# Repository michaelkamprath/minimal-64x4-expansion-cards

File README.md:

# Expansion Cards for Minimal 64x4 Computer
This repository contains various expansion cards for the [Minimal 64x4 Home Computer](https://github.com/slu4coder/Minimal-64x4-Home-Computer/) design by Carsten Herting, known as [slu4 on YouTube](https://www.youtube.com/channel/UCXYQcMpUBT3aaQKfmAVJNow).

## Back Plane
The [back plane provided in this repository](./expansion-backplane/) allows for more than one expansion card to be connected to the Minimal 64x4. It also provides a more convenient barrel jack power connector with a on/off switch to power the Minimal 64x4.

## Cards

* [**Speech Synthesizer**](./speech-synthesizer/) - This board provides support for interfacing with a TMS5220C speech synthesizer. 
* [**Multiplier Card**](./multiplier/) - This board provides a hardware implimentation of 8-bit integer multiplications, significantly improving the speed of multiplications over software-implementations.
* [**Timer**](./timer/) - Counts the cycles of the Minimal 64x4's system clock to enable precision timing of events.
* [**Joystick Adapter**](./joystick-adapter/) - Reads an Atari 2600 style joystick. Currently a breadboard prototype built behind the [breadboard adapter](./expansion-backplane/hardware/breadboard-connector/).

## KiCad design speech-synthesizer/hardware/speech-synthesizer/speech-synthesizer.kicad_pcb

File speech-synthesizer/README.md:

# TMS5220 Speech Synthesizer for Minimal 64x4 Computer
This project creates a TMS5220-based speech synthesizer board for the [Minimal 64x4](https://github.com/slu4coder/Minimal-64x4-Home-Computer) expansion port. The high-level design criteria are:

1. **Accommodate the “slow memory” nature of the TMS5220** by using hardware to buffer the interactions between the CPU and the TMS5220 such that the CPU is free to do other tasks while the TMS5220 processes data. This contrasts with typical 1980s computer hardware designs, which would halt the CPU while the TMS5220 processed data.
2. **Only support “external” speech data; PHROMs are not supported.** Not supporting PHROMs greatly simplifies the board and saves money, as original PHROMs are hard to come by in the modern age. Most games of the 1980s did not use PHROM data, instead providing their own LPC-encoded speech data.

This board supports both the TMS5220 and TMS5220C variants of the speech synthesizer chip.

## Hardware Design
The board responds to three memory-mapped addresses (the board is adjustable to set the `_` value below, but it defaults to `0xC`):

* `0xFE_0` – **TMS5220 Command Register**
  This address allows the host computer to write data to the TMS5220’s command register, which is used for sending “external speech” data to the TMS5220. In general, the host computer will write certain TMS5220 commands and speech data to this address.

* `0xFE_1` – **TMS5220 Status Register**
  This address allows the host computer to fetch the internal TMS5220 status register. To do that, the host computer writes some data to this address (any value, as the value is not actually used) to start the sequence of events to get the internal status from the TMS5220. When this is done, the status value will be readable by the host computer at this address. The status data being ready is indicated by the board’s `BUSY` line, which is readable at the **Board Status Register**. The `BUSY` line will be asserted high from the moment this address is written to until the status value is ready to be read.

* `0xFE_2` – **Board Status Register**
  This address exposes several internal states of this board, independent of the TMS5220, and can be read by the host computer at any time. The individual bits within the byte value read are below. Of these lines, the host computer generally only interacts with the `/INT` and `BUSY` bits.

  * **bit 0 – `BUSY`**
    Indicates whether the TMS5220 or the board, in general, is working on something. The host computer should not interact with the TMS5220 Command or Status registers while this bit is high. A write to the Command or Status register while `BUSY` is high is silently dropped: the board does not queue it and gives no error, so always poll `BUSY` low before each write.
  * **bit 1 – `/INT`**
    The current value of the active-low interrupt line coming out of the TMS5220. When this bit is low, it indicates that the TMS5220 requires attention. The specific issue can be determined by reading the TMS5220 Status Register.
  * **bit 2 – `/READY`**
    The current value of the active-low `READY` line out of the TMS5220. Host computer software should use the `BUSY` line to arbitrate interaction with the board, but the `READY` line is exposed here for diagnostic purposes.
  * **bit 3 – `WS`**
    The current status of the `WS` flip flop (active high). Exposed for diagnostic purposes.
  * **bit 4 – `RS`**
    The current status of the `RS` flip flop (active high). Exposed for diagnostic purposes.

* `0xFE_3` – **TMS5220C Reset** – *TMS5220C PLD variant only*
  The TMS5220C variant can be reset by holding both the `/RS` and `/WS` lines low at the same time. This action has undefined results for the non-C TMS5220 variant, so there are two versions of the ATF22V10C configuration in [pld-files](./pld-files/), and the one programmed must match the chip that is fitted:

  * `minimal-64x4-speech-controller-tms5220.pld` – for the original TMS5220. Writes to `0xFE_3` are ignored, so `/RS` and `/WS` can never be asserted together.
  * `minimal-64x4-speech-controller-tms5220c.pld` – for the TMS5220C. Adds the reset described here. Do not use it with an original TMS5220.

  With the TMS5220C variant, the host computer times the reset:

  1. Poll `BUSY` low, then write to `0xFE_3`. The board asserts `/RS` and `/WS` together. Write `0xFF`: the value is driven onto the TMS5220C data lines for the duration of the reset, and `0xFF` is also the TMS5220 reset command.
  2. Wait for the reset hold time. `BUSY` reads high for the whole reset.
  3. Write to `0xFE_3` again (this write is accepted even though `BUSY` is high). The board releases `/WS`, then `/RS` one clock later.
  4. Poll `BUSY` low before using the board again.

  The reset logic has been compiled and simulated but not yet tested on hardware, and the hold time the TMS5220C needs has not been measured.

### Supporting Circuitry
Besides the bus interface described below, the board has a few parts that keep the TMS5220 and its audio output well behaved:

* **Data line pull-downs.** The eight data lines between the TMS5220 and the two 74HCT374 latches are only driven during a read or a write. The rest of the time neither the TMS5220 nor the write latch `U5` drives them, so `RN2` (47K, 9-pin bussed SIP) pulls them to ground to keep the inputs of the read latch `U4` from floating. `RN2` sits between the `U5` and `U4` sockets, where each of its pins is next to a data pin of one of the two latches. It is a close fit: the footprints leave about 3.2 mm between the two socket bodies, so use a network with a body no thicker than 2.5 mm.
* **Local decoupling for the TMS5220.** `C11` and `C12` (100 nF) decouple the TMS5220's `+5V` and `-5V` supply pins to ground right at pins 5 and 4, and `C13` (10 µF) adds bulk capacitance to the `-5V` rail from the converter module. `C13` is polarized: because it sits on a negative rail, its positive lead goes to ground.
* **Audio output.** The TMS5220's speaker pin is a current output. `R1` (1K8) converts it to a voltage and `C2` filters it, `C1` AC-couples the result to the 3.5 mm jack, and `R2` (100K) bleeds the jack side of `C1` to ground so that plugging in a cable does not pop.

### TMS5220 “Slow Memory” Issue
A key pin to understand on the TMS5220 is the `READY` signal at pin 18. The TMS5220 drives the `READY` pin low when it is ready to accept input or provide output to the host computer. When the `READY` pin is high, the TMS5220 is busy processing data and does not immediately act on—if not outright ignore—any interactions the CPU initiates. In many 1980s-era computers, the `READY` pin was connected to the CPU’s halt or wait-state pin, causing the CPU to stop while the TMS5220 processed data. This board takes a different approach. In some ways, this is necessary because the Minimal 64x4 has no line that would allow an accessory to pause or halt the CPU. However, this design choice is otherwise agnostic of that limitation.

As a result, data interactions between the host computer and the TMS5220 must be cached to handle the timing differences. The key to caching these CPU interactions is the ATF22V10C programmable logic chip and the 74HCT74 flip flops. The flip flops hold the `/WS` and `/RS` signals on the TMS5220, and the ATF22V10C is programmed to create a state machine that manages these flip flops. For example, here is the sequence of events for writing a byte of data to the TMS5220:

1. When the address bus is set to the memory-mapped address of `0xFEC0`, the 74HCT688s will assert this `MMAP` line, and the `M0` and `M1` address lines will be 0. To write to the TMS5220, the host computer `/RI` line will be asserted. The ATF22V10C’s programmable logic then asserts `WS_CLK`, which is the clock line that drives the `WS` flip flop, in turn asserting the active-low `/WS` line to the TMS5220. This tells the TMS5220 that we want to write data to its data lines.
2. At the same time `WS_CLK` causes the `WS` flip flop to set its state, `WS_CLK` also causes the data bus input 74HCT374 flip flop to load the contents of the host computer’s data bus. Because of this, the expansion board can capture and hold the data bus value the host computer is writing to the TMS5220, allowing the host computer to move on to other tasks while this flip flop holds the data bus value. Furthermore, the `/WS` line to the TMS5220 also drives the output enable on the 74HCT374 octal flip flop, so the buffered data will be held and driven onto the board’s internal data bus for the entire time `/WS` is low—even as the host computer does other work. This is the essence of the “slow memory” issue: the TMS5220 requires several host-computer clock cycles to read in the data, and its data lines must be held for the entire duration. The 74HCT374 flip flop buffers the data and holds the lines active as long as needed.
3. In response to the `/WS` line being asserted, the TMS5220 drives the `READY` line high. When this occurs, the ATF22V10C waits until the `READY` line transitions from high to low, which indicates that the TMS5220 has finished processing the input data. When the `READY` line goes low, the ATF22V10C then asserts `WS_RST`, the reset line for the `WS` flip flop. This brings `/WS` high, which tells the TMS5220 that the write operation is complete. It also disables the output enable on the 74HCT374 that was buffering the data. In this way, `/WS` remains asserted until the TMS5220 indicates it is done reading the data from the buffers, as indicated by the `READY` line.
4. During this entire sequence, the ATF22V10C asserts the `BUSY` line for the board, which can be read by the host computer at address `0xFE_2` via the 74HCT245. This allows the host computer to query the board to see if the TMS5220 is done processing data.

A similar sequence is used when reading data from the TMS5220, centered around the `/RS` line.

### Undocumented Timing Issues
The TMS5220 appears to have some timing requirements that are not documented in its datasheet. These requirements were exposed by the Minimal 64x4, which runs at a clock speed faster than the typical host computers for which the TMS5220 was designed. These undocumented timing requirements were determined empirically and could likely be tweaked further:

* **Read Cycle for Status Transfers to External Speech Data Write**
  The datasheet indicates that the `t_wait` after `/RS` goes high is 12 µs. However, I found that something closer to 175 µs was needed between a status read and a subsequent external speech data write.

* **External Speech Data Write to Read Cycle for Status Transfers**
  Similarly, extra time is needed between writing external speech data and then reading the TMS5220 status. Again, I found that about 175 µs was needed.

These values were “tweaked until it worked.” The issues seem related to switching modes of interaction with the TMS5220. By contrast, writing an external speech data byte after a prior external speech data byte does adhere to the timing diagrams in the TMS5220 datasheet. Further experimentation might uncover better or smaller delays for these undocumented requirements.

## Software Design
The provided `speechlib.min64x4` file contains all the subroutines needed to use this board on the Minimal 64x4 home computer:

* `speech_init`
  Call this to initialize the board.

* `speak_synchronous`
  Speaks the LPC data in a passed buffer synchronously. Push the following arguments on the stack (in push order):
  1. **Buffer End Address** – 2-byte end address of the data buffer
  2. **Buffer Start Address** – 2-byte start address of the data buffer

* `speech_start`
  Speaks the LPC data in a passed buffer asynchronously, after synchronously waiting for any currently active talking to finish. Push the following arguments on the stack (in push order):
  1. **Buffer End Address** – 2-byte end address of the data buffer
  2. **Buffer Start Address** – 2-byte start address of the data buffer

* `speech_start_if_not_talking`
  Speaks the LPC data in a passed buffer asynchronously if there is no currently active speech. Push the following arguments on the stack (in push order):
  1. **Buffer End Address** – 2-byte end address of the data buffer
  2. **Buffer Start Address** – 2-byte start address of the data buffer

* `speech_update_buffer`
  Call this periodically (about every 1 ms) to enable asynchronous speech. No arguments.

* `speech_get_status`
  Gets the contents of the TMS5220 status register, which is returned in the `A` register. The following bit masks are defined to help interpret the results:
  * `SPEECH_STATUS_TALK` – The TMS5220 is currently talking.
  * `SPEECH_STATUS_BUFFER_LOW` – The TMS5220 FIFO buffer is half-empty. More LPC data needs to be sent.
    *_Note_*: The `speech_update_buffer` function automatically updates the FIFO if needed.
  * `SPEECH_STATUS_BUFFER_EMPTY` – The TMS5220 FIFO buffer is empty.

# Compiling the Software
All software found in the [software](./software/) directory is compiled with [BespokeASM](https://github.com/michaelkamprath/bespokeasm), which supports the Minimal 64x4. [Carsten Herting](https://github.com/slu4coder), the creator of the Minimal 64x4, also provides an assembler for it, but that assembler is quite minimal. One key shortcoming is the inability to import library code into the current compilation. BespokeASM enables importing libraries and includes several other features that this project’s software depends on.

To compile the speech code in this repository, use the following command:

```sh
bespokeasm compile -c /path/to/bespokeasm/examples/slu4-minimal-64x4/slu4-minimal-64x4.yaml -n -p -t intel_hex lpc_player.min64x4
```
Where `/path/to/bespokeasm` is the path to the BespokeASM repository on your computer. This will produce an Intel HEX representation of the compiled program, which can then be sent to the Minimal 64x4 using its `receive` command.

# Resources
The following resources I found useful when putting together this project

* [TMS5220 Datasheet](./datasheets/tms5220.pdf) - Always consult the datasheet first.
* [Thierry Nouspikel's "The Speech Synthesizer module"](https://www.unige.ch/medecine/nouspikel/ti99/speech.htm) - A detailed overview of how the TMS5220 is used in the TI 99/4a.
* [TI 99/4a Development forum on AtariAge](https://forums.atariage.com/topic/352156-looking-for-help-on-tms5220-circuit-software-design-and-usage/) - These folks are legends, helpful and knowledgable about anything related to Texas Instruments.

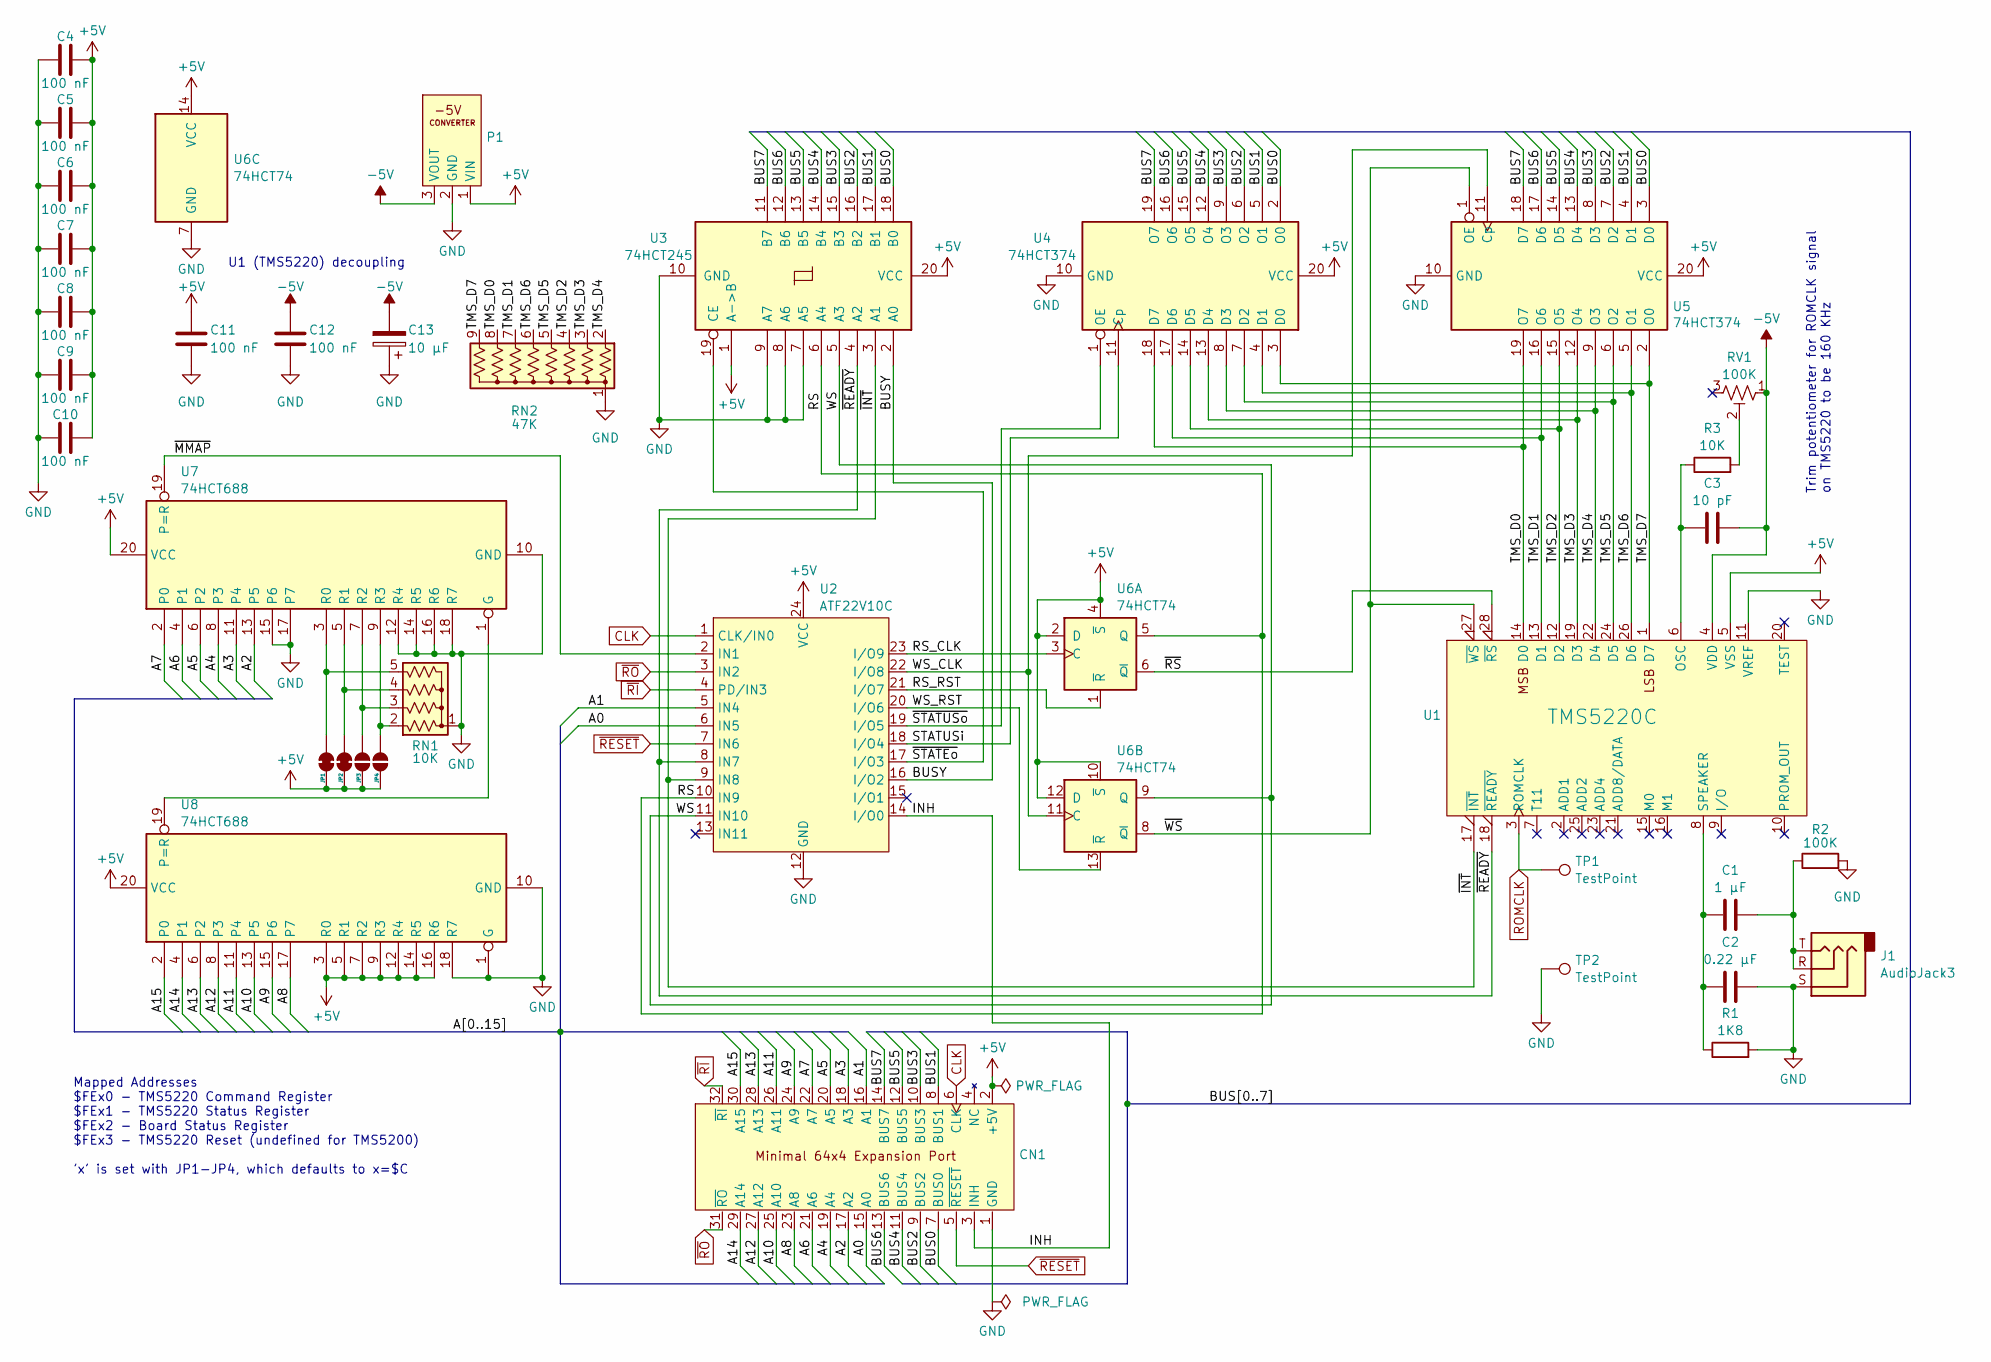
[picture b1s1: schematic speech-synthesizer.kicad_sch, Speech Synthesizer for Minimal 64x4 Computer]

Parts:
C1: 1 µF; C_Disc_D4.7mm_W2.5mm_P5.00mm
C2: 0.22 µF; C_Disc_D4.7mm_W2.5mm_P5.00mm
C3: 10 pF; C_Disc_D5.0mm_W2.5mm_P2.50mm
C4, C5, C6, C7, C8, C9, C10, C11, C12: 100 nF; C_Disc_D3.4mm_W2.1mm_P2.50mm
C13: 10 µF; CP_Radial_D5.0mm_P2.00mm
CN1: PinHeader_2x16_P2.54mm_Horizontal
J1: AudioJack3; Jack_3.5mm_CUI_SJ1-3523N_Horizontal
JP1, JP2: SolderJumper_2_Bridged; SolderJumper-2_P1.3mm_Bridged_RoundedPad1.0x1.5mm
JP3, JP4: SolderJumper_2_Open; SolderJumper-2_P1.3mm_Open_RoundedPad1.0x1.5mm
P1: -5V_Converter
R1: 1K8; R_Axial_DIN0207_L6.3mm_D2.5mm_P10.16mm_Horizontal
R2: 100K; R_Axial_DIN0207_L6.3mm_D2.5mm_P10.16mm_Horizontal
R3: 10K; R_Axial_DIN0207_L6.3mm_D2.5mm_P10.16mm_Horizontal
RN1: 10K; R_Array_SIP5
RN2: 47K; R_Array_SIP9
RV1: 100K; Potentiometer_Vishay_T73YP_Vertical
TP1, TP2: TestPoint; TestPoint_Pad_D2.0mm
U1: TMS5220C; DIP-28_W15.24mm_Socket
U2: ATF22V10C; DIP-24_W7.62mm_Socket
U3: 74HCT245; DIP-20_W7.62mm_Socket
U4, U5: 74HCT374; DIP-20_W7.62mm_Socket
U6: 74HCT74; DIP-14_W7.62mm_Socket
U7, U8: 74HCT688; DIP-20_W7.62mm_Socket

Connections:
+5V: C4.2, C5.2, C6.2, C7.2, C8.2, C9.2, C10.2, C11.1, CN1.2 (+5V), JP1.1 (A), JP2.1 (A), JP3.1 (A), JP4.1 (A), P1.1 (VIN), U1.5 (VSS), U2.24 (VCC), U3.1 (A->B), U3.20 (VCC), U4.20 (VCC), U5.20 (VCC), U6.2 (D), U6.4 (~S), U6.10 (~S), U6.12 (D), U6.14 (VCC), U7.20 (VCC), U8.3 (R0), U8.5 (R1), U8.7 (R2), U8.9 (R3), U8.12 (R4), U8.14 (R5), U8.16 (R6), U8.20 (VCC)
-5V: C3.1, C12.1, C13.2, P1.3 (VOUT), RV1.1, U1.4 (VDD)
/A0: CN1.15 (A0), U2.6 (IN5)
/A1: CN1.16 (A1), U2.5 (IN4)
/A2: CN1.17 (A2), U7.13 (P5)
/A3: CN1.18 (A3), U7.11 (P4)
/A4: CN1.19 (A4), U7.8 (P3)
/A5: CN1.20 (A5), U7.6 (P2)
/A6: CN1.21 (A6), U7.4 (P1)
/A7: CN1.22 (A7), U7.2 (P0)
/A8: CN1.23 (A8), U8.17 (P7)
/A9: CN1.24 (A9), U8.15 (P6)
/A10: CN1.25 (A10), U8.13 (P5)
/A11: CN1.26 (A11), U8.11 (P4)
/A12: CN1.27 (A12), U8.8 (P3)
/A13: CN1.28 (A13), U8.6 (P2)
/A14: CN1.29 (A14), U8.4 (P1)
/A15: CN1.30 (A15), U8.2 (P0)
/BUS0: CN1.7 (BUS0), U3.18 (B0), U4.2 (O0), U5.3 (D0)
/BUS1: CN1.8 (BUS1), U3.17 (B1), U4.5 (O1), U5.4 (D1)
/BUS2: CN1.9 (BUS2), U3.16 (B2), U4.6 (O2), U5.7 (D2)
/BUS3: CN1.10 (BUS3), U3.15 (B3), U4.9 (O3), U5.8 (D3)
/BUS4: CN1.11 (BUS4), U3.14 (B4), U4.12 (O4), U5.13 (D4)
/BUS5: CN1.12 (BUS5), U3.13 (B5), U4.15 (O5), U5.14 (D5)
/BUS6: CN1.13 (BUS6), U3.12 (B6), U4.16 (O6), U5.17 (D6)
/BUS7: CN1.14 (BUS7), U3.11 (B7), U4.19 (O7), U5.18 (D7)
/BUSY: U2.16 (I/O2), U3.2 (A0)
/INH: CN1.3 (INH), U2.14 (I/O0)
/RS: U2.10 (IN9), U3.6 (A4), U6.5 (Q)
/RS_CLK: U2.23 (I/O9), U6.3 (C)
/RS_RST: U2.21 (I/O7), U6.1 (~R)
/STATUSi: U2.18 (I/O4), U4.11 (Cp)
/TMS_D0: RN2.8 (R7), U1.14 (D0), U4.18 (D7), U5.19 (O7)
/TMS_D1: RN2.7 (R6), U1.13 (D1), U4.17 (D6), U5.16 (O6)
/TMS_D2: RN2.4 (R3), U1.12 (D2), U4.14 (D5), U5.15 (O5)
/TMS_D3: RN2.3 (R2), U1.19 (D3), U4.13 (D4), U5.12 (O4)
/TMS_D4: RN2.2 (R1), U1.22 (D4), U4.8 (D3), U5.9 (O3)
/TMS_D5: RN2.5 (R4), U1.24 (D5), U4.7 (D2), U5.6 (O2)
/TMS_D6: RN2.6 (R5), U1.26 (D6), U4.4 (D1), U5.5 (O1)
/TMS_D7: RN2.9 (R8), U1.1 (D7), U4.3 (D0), U5.2 (O0)
/WS: U2.11 (IN10), U3.5 (A3), U6.9 (Q)
/WS_CLK: U2.22 (I/O8), U5.11 (Cp), U6.11 (C)
/WS_RST: U2.20 (I/O6), U6.13 (~R)
/~INT: U1.17 (~INT), U2.9 (IN8), U3.3 (A1)
/~MMAP: U2.2 (IN1), U7.19 (P=R)
/~READY: U1.18 (~READY), U2.8 (IN7), U3.4 (A2)
/~RS: U1.28 (~RS), U6.6 (~Q)
/~STATEo: U2.17 (I/O3), U3.19 (CE)
/~STATUSo: U2.19 (I/O5), U4.1 (OE)
/~WS: U1.27 (~WS), U5.1 (OE), U6.8 (~Q)
CLK: CN1.6 (CLK), U2.1 (CLK/IN0)
GND: C2.2, C4.1, C5.1, C6.1, C7.1, C8.1, C9.1, C10.1, C11.2, C12.2, C13.1, CN1.1 (GND), J1.S, P1.2 (GND), R1.2, R2.2, RN1.1 (common), RN2.1 (common), TP2.1, U1.11 (VREF), U2.12 (GND), U3.7 (A5), U3.8 (A6), U3.9 (A7), U3.10 (GND), U4.10 (GND), U5.10 (GND), U6.7 (GND), U7.10 (GND), U7.12 (R4), U7.14 (R5), U7.15 (P6), U7.16 (R6), U7.17 (P7), U7.18 (R7), U8.1 (G), U8.10 (GND), U8.18 (R7)
unnamed: C1.2, J1.R, J1.T, R2.1
unnamed: JP1.2 (B), RN1.5 (R4), U7.3 (R0)
unnamed: JP2.2 (B), RN1.4 (R3), U7.5 (R1)
unnamed: JP3.2 (B), RN1.3 (R2), U7.7 (R2)
unnamed: JP4.2 (B), RN1.2 (R1), U7.9 (R3)
unnamed: R3.2, RV1.2
unnamed: C3.2, R3.1, U1.6 (OSC)
unnamed: C1.1, C2.1, R1.1, U1.8 (SPEAKER)
unnamed: U7.1 (G), U8.19 (P=R)
ROMCLK: TP1.1, U1.3 (ROMCLK)
~RESET: CN1.5 (~RESET), U2.7 (IN6)
~RI: CN1.32 (~RI), U2.4 (PD/IN3)
~RO: CN1.31 (~RO), U2.3 (IN2)

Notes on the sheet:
Trim potentiometer for ROMCLK signal on TMS5220 to be 160 KHz
Mapped Addresses $FEx0 - TMS5220 Command Register $FEx1 - TMS5220 Status Register $FEx2 - Board Status Register $FEx3 - TMS5220 Reset (undefined for TMS5200) 'x' is set with JP1-JP4, which defaults to x=$C
U1 (TMS5220) decoupling

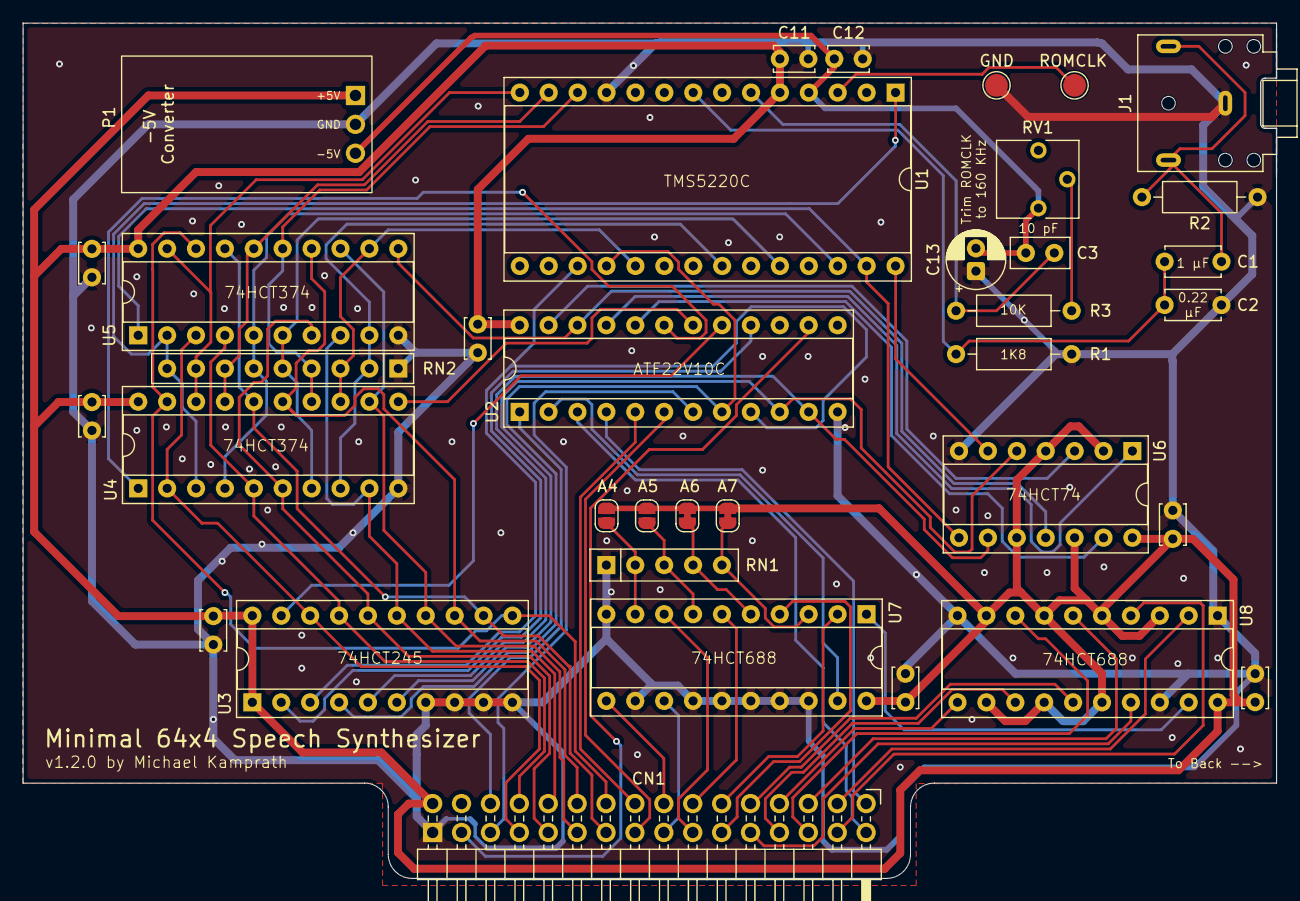
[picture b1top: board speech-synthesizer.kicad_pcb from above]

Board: 2 copper layers, 110.2 x 75.2 mm, 36 parts (0 on the bottom side), 65 nets.

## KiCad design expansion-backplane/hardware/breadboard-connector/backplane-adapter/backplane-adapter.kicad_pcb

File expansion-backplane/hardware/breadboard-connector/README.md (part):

# Minimal 64x4 Breadboard Prototyping Adapter

Bench tooling for prototyping Minimal 64x4 expansion cards on a solderless breadboard before designing their PCBs. The adapter plugs into a slot of the [expansion backplane](../expansion-backplane/), or directly into the Minimal's expansion port, and brings a buffered, address-decoded view of the expansion bus to a breadboard over a ribbon cable.

The design requirements are in [`breadboard-adapter-design-prompt.md`](breadboard-adapter-design-prompt.md).

## Boards

| Directory | Board | Role |
|---|---|---|
| [`backplane-adapter/`](backplane-adapter/) | Board A | Plugs into a backplane slot. Buffers all signals, decodes the `$FE` page plus a switch-selected 16-byte base window, drives INH, and protects the Minimal from the breadboard. |
| [`breadboard-breakout/`](breadboard-breakout/) | Board B | Receives the cable and the twisted power pair from Board A's J2, and brings every signal to labeled 0.1 inch headers that plug into a breadboard. |

The two boards are separate KiCad projects. Both use the shared symbol and footprint libraries in [`kicad-libraries/`](../../../kicad-libraries/).

## Cable pinout

**This table is the single source of truth for the ribbon cable.** The two boards are in separate KiCad projects, so nothing checks automatically that both ends agree. Any change to the cable connector on either schematic must be made here first, then applied to both boards.

Cable: 40-way, 0.05 inch pitch IDC ribbon, 30 to 45 cm (see [Cable length](#cable-length) for what the length costs). Every signal conductor has a ground conductor on each side. The clock and both strobes must sit between two grounds.

Status: **proposed**, as drawn on Board A J1. Every odd pin is ground, so along the ribbon every signal (even pin) sits between two grounds. Pin 40 is an extra ground. No logic power rides on the ribbon. `~MATCH` is active low; `INH_REQ` is active high.

| Pin | Signal | Pin | Signal |
|---|---|---|---|
| 1 | GND | 2 | A0 |
| 3 | GND | 4 | A1 |
| 5 | GND | 6 | A2 |
| 7 | GND | 8 | A3 |
| 9 | GND | 10 | ~MATCH (16-byte base window) |
| 11 | GND | 12 | ~RO |
| 13 | GND | 14 | ~RI |
| 15 | GND | 16 | CLK |
| 17 | GND | 18 | INH_REQ (breadboard to adapter) |
| 19 | GND | 20 | BUS0 |
| 21 | GND | 22 | BUS1 |
| 23 | GND | 24 | BUS2 |
| 25 | GND | 26 | BUS3 |
| 27 | GND | 28 | BUS4 |
| 29 | GND | 30 | BUS5 |
| 31 | GND | 32 | BUS6 |
| 33 | GND | 34 | BUS7 |
| 35 | GND | 36 | ~RESET (unbuffered pass-through) |
| 37 | GND | 38 | USER (unbuffered pass-through) |
| 39 | GND | 40 | GND |

Main +5 V and ground to the breadboard use a separate 20 or 22 AWG twisted pair from Board A's J2 to Board B, not the ribbon.

## Using the adapter

### Power

- **JP1 fitted (normal use):** the breadboard is powered from the backplane, or from the Minimal when Board A plugs directly into its expansion port, through F1 and J2. One supply powers both sides, so they always switch on and off together. F1, a 0.5 A resettable fuse, limits what a breadboard fault can draw through the Minimal's or the backplane's 5 V path; it trips at about 1 A and resets once the fault is removed and it cools. A prototype that needs more than a few hundred mA should use its own supply on Board B's J3, with JP1 removed. When Board A plugs directly into the Minimal, the computer may be running from its UART's USB power, which leaves only a few hundred mA for the breadboard.
- **JP1 removed:** J2's +5 V is disconnected and the breadboard needs its own supply. Ground stays common through J2 and the ribbon. **Switch both supplies on and off together.** If one side is powered and the other is not, the powered side's drivers push current through the 33 Ω termination into the unpowered chips' input protection diodes, on the order of 100 mA per line. That is an operating error, not a design fault, but it can damage parts on either side.

### Enable switch

SW2 is **closed for enabled**. With it open, the adapter is disconnected from the bus: the data transceiver (U4) is off and INH is held low. A freshly built adapter therefore does nothing until SW2 is switched on.

## Who drives the data bus

This document names bus operations from the CPU's side and always says "CPU read" or "CPU write". Seen from the prototype, each one is the opposite action on the data bus:

| Operation | Strobe | Who drives the data bus | What the prototype does | INH_REQ |
|---|---|---|---|---|
| **CPU read** | `~RO` low, `~RI` high | The prototype (through U4, toward the backplane) | Puts its data on the bus | The prototype must raise it |
| **CPU write** | `~RI` low | The CPU (through U4, toward the breadboard) | Takes the data from the bus on the rising edge of CLK | Not used |

The strobe names follow the Minimal's RAM: `~RO` is "RAM out" (the addressed device drives the bus) and `~RI` is "RAM in" (the addressed device takes data from the bus).

## Rules for a breadboard prototype

The adapter keeps a misbehaving breadboard from damaging the Minimal, but a prototype that follows these rules behaves like a real card and avoids fighting the adapter's own drivers:

1. **Decode from `~MATCH` and A0..A3.** `~MATCH` is low for every access to the 16-byte window set by SW1. A4..A15 are not on the cable.
2. **Raise INH_REQ only for a CPU read of one of your registers** (the prototype drives the data bus), qualified by `~RO` low and `~RI` high, the same way the [timer card's PLD](../../../timer/pld-files/timer.pld) qualifies its INH. The adapter ignores INH_REQ outside CPU reads anyway, but qualifying it keeps the prototype honest for its final PCB.
3. **Drive the breadboard's data bus only while `~RO` is low** (and you are raising INH_REQ). Outside those cycles the adapter's U4 drives the cable side of the data bus toward the breadboard, so a prototype that drives early fights U4 through the 33 Ω termination: current-limited, no damage, but messy waveforms.
4. **Keep the decode fast.** The prototype has about 14 ns, worst case, from its inputs to INH_REQ (see the timing estimate below). One pass through a -7 PLD (ATF16V8C or ATF22V10C) or two 74AHCT gates fits. A 74HC decode chain does not.
5. **Capture CPU writes (the CPU drives the data bus) on the rising edge of CLK while `~RI` is low**, not on `~RI`'s rising edge. See the CPU write timing below.
6. **Never drive `~RESET` high.** It is wired straight through to the Minimal's reset line. Only pull it low (Board B's button does this).

## Drawing a prototype's schematic

The shared symbol library (`kicad-libraries/minimal-64x4.kicad_sym`) has a symbol, `min-64x4-breadboard-adapter`, that stands for the whole adapter as the breadboard sees it. A prototype's schematic uses it in place of the expansion connector and does not need to show Board A or Board B.

- **Signals:** A0..A3, `~MATCH`, `~RO`, `~RI` and CLK are outputs of the adapter. BUS0..BUS7 are bidirectional. INH_REQ is an input to the adapter; Board A pulls it low, so a prototype that never drives the data bus (the CPU only writes to it) can leave it unconnected (mark it no-connect).
- **Power:** +5 V and GND are power inputs, as on the expansion-port symbol, so add `PWR_FLAG` symbols to those nets.
- **Pin numbers** are Board B's pin positions in DIP-24 order, looking at the top of the board with the cable connector away from you: 1 to 12 down the left row (+5 V, GND, USER, `~RESET`, BUS7..BUS0), 13 to 24 up the right row (GND, INH_REQ, CLK, `~RI`, `~RO`, `~MATCH`, A3..A0, GND, +5 V). The rows are 7.62 mm apart, so a DIP-24 socket footprint matches the pins if a later PCB should accept Board B directly.
- The symbol is excluded from the BOM and from the board by default.

## Building a prototype's logic

### Timing budget

A prototype's logic has two budgets, both counted from the moment its inputs arrive on the breadboard. The inputs that matter are the later of `~MATCH` and `~RO`, after U3 and the ribbon. They arrive about 57 ns after the CPU's clock edge typically, 67 ns at the 25 °C maximum, and 76 ns at the −40..85 °C maximum. On a CPU read, the prototype's data must be on the backplane by about 115 ns (see the timing estimate below).

| From inputs at the breadboard to... | Typ | Max 25 °C | Max −40..85 °C |
|---|---|---|---|
| **INH_REQ out** (X in the timing estimate) | 39 ns | 24 ns | **14 ns** |
| **Prototype's data driven onto the cable** (CPU read) | 50 ns | 37 ns | **27 ns** |

The second budget covers the ribbon and U4's A-to-B delay on the way back to the backplane.

- **ATF16V8C-7 (7.5 ns):** fits both budgets, with 7 ns to spare at the worst case. A -10 part also fits. A -15 part misses the worst case by about 1 ns but is fine at room temperature.
- **Data drivers:** after the PLD's 7.5 ns, about 20 ns remain for the output enable of whatever drives the data bus. A 74AHCT245 or 74AHCT541 (16 ns max) fits. For anything slower, such as a counter's own output enable, check its datasheet. If it is over about 20 ns, put a 74AHCT245 or 541 in front of it.
- **INH release** rarely depends on the prototype. Board A's PLD raises INH only while INH_REQ is high, `~RO` is low, `~RI` is high and its own decode matches the window, and drops it as soon as any one of those stops being true. Leaving the window and the end of the CPU read are both seen on Board A directly. The one case that waits for the prototype is described under [INH release](#inh-release-and-the-following-opcode-fetch).

### A nominal ATF16V8C

[`pld-files/breadboard-prototype-template.pld`](pld-files/breadboard-prototype-template.pld) is a starting point that compiles with galette. Its example register map uses the window `$FEx0..$FEx3`, where `x` is the base nibble set by SW1:

| Address | CPU write | CPU read |
|---|---|---|
| `$FEx0` | WR0 | RD0 (INH_REQ) |
| `$FEx1` | WR1 | RD1 (INH_REQ) |
| `$FEx2` | WR2 | RD2 (INH_REQ) |
| `$FEx3` | WR3 | nothing; the CPU reads RAM |
| `$FEx4..$FExF` | nothing | nothing |

How it is put together:

- **INH_REQ repeats the CPU-read decode instead of ORing the RD outputs.** The timer card's PLD does `INH = /OE0 + /OE1 + ...`, which feeds outputs back into the array: a second PLD pass. On the breadboard that would double X to 15 ns, over the 14 ns worst-case budget.
- **The CPU-write strobes (WR0..WR3) are registered on CLK with `~RI` low**, like `WS_CLK.R` on the speech card. Each strobe rises one clock-to-output delay after the cable's CLK edge and lasts exactly one cycle.
- **Clock each data latch (74AHCT374 or 574) on its strobe's rising edge.** The CPU's data stays on the bus for roughly 25 ns after that edge. The falling edge comes a cycle later, after the data is gone, which is why the strobes are active high.
- **Registered mode costs two pins.** Pin 1 becomes the register clock and pin 11 the registered outputs' `/OE`, which must be tied to GND. That leaves 8 outputs: in the template, INH_REQ, four CPU-write strobes and three CPU-read enables (RD0..RD2, which turn on the prototype's bus drivers). A prototype with no registers for the CPU to write gets pins 1 and 11 back as inputs.
- **`~RESET` is on pin 9** for clearing prototype state. No equation in the template uses it yet.
- **A0..A3 hold time at the CPU-write sample is tight**, by a few ns, on every card. The Minimal can change the address 10 to 15 ns after the clock edge, about when the port's CLK, one 74HC32 behind the CPU's clock, arrives. The adapter makes this no worse, because CLK and A0..A3 pass through U3 together.

## Timing estimate (CPU read through the adapter)

### The Minimal's CPU read cycle

From the "Timing Signals" section of the [Minimal 64x4 manual](https://docs.google.com/document/d/1-nDv_8WEG1FrlO3kEK0icoYo-Z-jlhpCMiCstxGOCjQ/edit?usp=sharing). Its diagram was measured on the author's board at 8.3 MHz and 5 V, with every time referenced to the CPU clock's rising edge at the start of the cycle. The [Revision 1.1 schematic](https://github.com/slu4coder/Minimal-64x4-Home-Computer/blob/main/Revision%201.1/Schematics.pdf) shows how the port's signals connect:

- **`~RO` and `~RI`** (port pins 31 and 32) come straight from the control-word FLASH (U21), with no gating. They are the same `~RO` that drives the RAM's and FLASH's output enables. Port `~RI` is the control-word level, not the RAM write pulse: the SRAM's `~WE` is `~RI_PLS`, which is `~RI` ORed with a short clock pulse (U7D) near the edge that ends the cycle.
- **CLK** (port pin 6) is `CLK_PC` through one 74HC32 gate (U33C), so it lags the CPU's clock edge by one gate delay.
- **INH** (port pin 3) has a 4.7 kΩ pulldown and drives the SRAM's `~CE` directly. In the `$FE` page the FLASH is already deselected by A15.

| Event | Time after the rising edge |
|---|---|
| Address lines (MAR outputs) change | 0 to 15 ns |
| Control word settles, including the port's `~RO` and `~RI` | 45 to 50 ns, and stays until 45 to 50 ns into the next cycle |
| The Minimal's own RAM drives its data onto the bus | about 80 ns |
| Bus sampled | at the next rising edge, with 10 ns setup required |

At 8 MHz (125 ns cycle), **on a CPU read, the addressed device's data must be on the backplane bus by about 115 ns.** The address can change in the same cycle as the CPU read: in `LDB` the MAR is loaded at the edge that starts the CPU read step, so the address path starts at 15 ns, not at 0. These are measured, typical values. The manual notes that 74HC switching slows by about 20 % at 4.5 V.

### The adapter's two paths

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
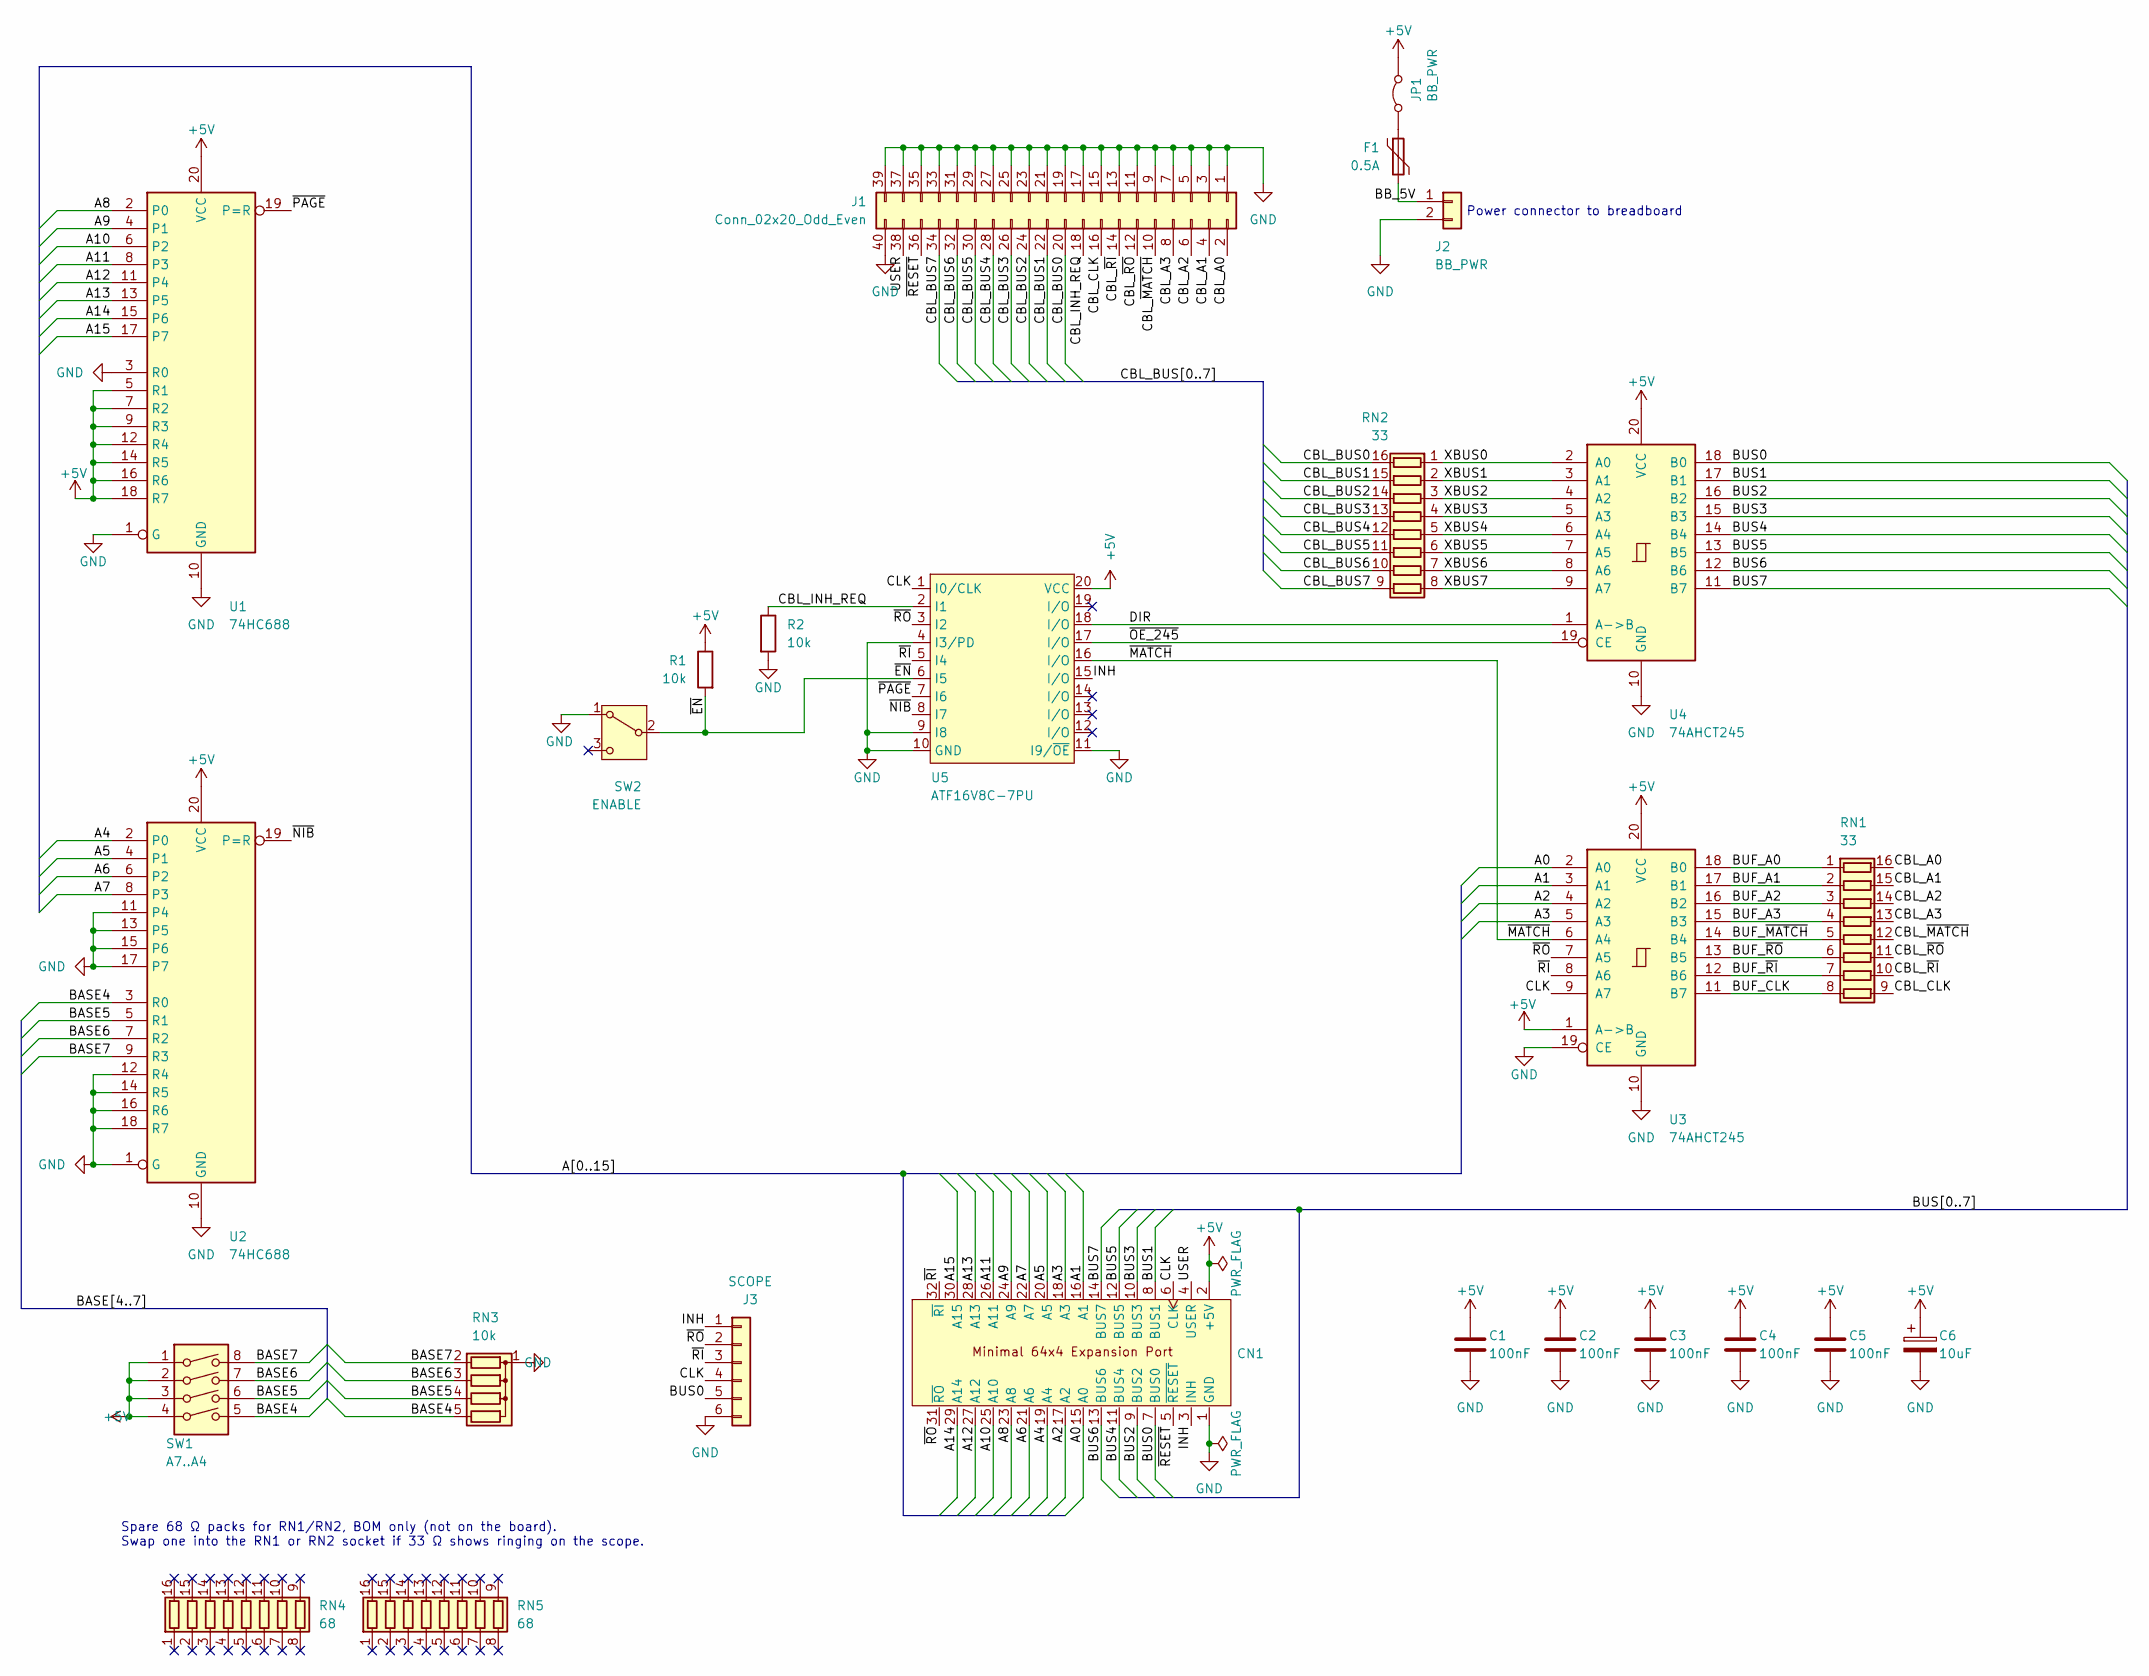
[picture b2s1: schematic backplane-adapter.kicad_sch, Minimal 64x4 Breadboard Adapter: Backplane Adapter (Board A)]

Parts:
C1, C2, C3, C4, C5: 100nF; C_Disc_D3.4mm_W2.1mm_P2.50mm
C6: 10uF; CP_Radial_D5.0mm_P2.00mm
CN1: Minimal64x4_Expansion_Card_Connector
F1: 0.5A; Fuse_Bourns_MF-RHT050; Manufacturer Part Number Bourns MF-RHT050
J1: Conn_02x20_Odd_Even; IDC-Header_2x20_P2.54mm_Horizontal; Manufacturer Part Number Sullins SBH11-PBPC-D20-RA-BK
J2: BB_PWR; TerminalBlock_Phoenix_MKDS-1,5-2-5.08_1x02_P5.08mm_Horizont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
J3: SCOPE; PinHeader_1x06_P2.54mm_Horizontal
JP1: BB_PWR; PinHeader_1x02_P2.54mm_Vertical
R1, R2: 10k; R_Axial_DIN0207_L6.3mm_D2.5mm_P7.62mm_Horizontal
RN1, RN2: 33; DIP-16_W7.62mm_Socket; Mouser Part Number 652-4116R-1-330LF
RN3: 10k; R_Array_SIP5
RN4, RN5: 68; DIP-16_W7.62mm_Socket; Mouser Part Number 652-4116R-1-680LF
SW1: A7..A4; SW_DIP_SPSTx04_Slide_9.78x12.34mm_W7.62mm_P2.54mm
SW2: ENABLE; SW_Slide_SPDT_Angled_CK_OS102011MA1Q
U1, U2: 74HC688; DIP-20_W7.62mm_Socket
U3, U4: 74AHCT245; DIP-20_W7.62mm_Socket
U5: ATF16V8C-7PU; DIP-20_W7.62mm_Socket

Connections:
+5V: C1.1, C2.1, C3.1, C4.1, C5.1, C6.1, CN1.2 (+5V), JP1.2 (B), R1.1, SW1.1, SW1.2, SW1.3, SW1.4, U1.5 (R1), U1.7 (R2), U1.9 (R3), U1.12 (R4), U1.14 (R5), U1.16 (R6), U1.18 (R7), U1.20 (VCC), U2.20 (VCC), U3.1 (A->B), U3.20 (VCC), U4.20 (VCC), U5.20 (VCC)
/A0: CN1.15 (A0), U3.2 (A0)
/A1: CN1.16 (A1), U3.3 (A1)
/A2: CN1.17 (A2), U3.4 (A2)
/A3: CN1.18 (A3), U3.5 (A3)
/A4: CN1.19 (A4), U2.2 (P0)
/A5: CN1.20 (A5), U2.4 (P1)
/A6: CN1.21 (A6), U2.6 (P2)
/A7: CN1.22 (A7), U2.8 (P3)
/A8: CN1.23 (A8), U1.2 (P0)
/A9: CN1.24 (A9), U1.4 (P1)
/A10: CN1.25 (A10), U1.6 (P2)
/A11: CN1.26 (A11), U1.8 (P3)
/A12: CN1.27 (A12), U1.11 (P4)
/A13: CN1.28 (A13), U1.13 (P5)
/A14: CN1.29 (A14), U1.15 (P6)
/A15: CN1.30 (A15), U1.17 (P7)
/BASE4: RN3.5 (R4), SW1.5, U2.3 (R0)
/BASE5: RN3.4 (R3), SW1.6, U2.5 (R1)
/BASE6: RN3.3 (R2), SW1.7, U2.7 (R2)
/BASE7: RN3.2 (R1), SW1.8, U2.9 (R3)
/BB_5V: F1.2, J2.1
/BUF_A0: RN1.1 (R1.1), U3.18 (B0)
/BUF_A1: RN1.2 (R2.1), U3.17 (B1)
/BUF_A2: RN1.3 (R3.1), U3.16 (B2)
/BUF_A3: RN1.4 (R4.1), U3.15 (B3)
/BUF_CLK: RN1.8 (R8.1), U3.11 (B7)
/BUF_~MATCH: RN1.5 (R5.1), U3.14 (B4)
/BUF_~RI: RN1.7 (R7.1), U3.12 (B6)
/BUF_~RO: RN1.6 (R6.1), U3.13 (B5)
/BUS0: CN1.7 (BUS0), J3.5, U4.18 (B0)
/BUS1: CN1.8 (BUS1), U4.17 (B1)
/BUS2: CN1.9 (BUS2), U4.16 (B2)
/BUS3: CN1.10 (BUS3), U4.15 (B3)
/BUS4: CN1.11 (BUS4), U4.14 (B4)
/BUS5: CN1.12 (BUS5), U4.13 (B5)
/BUS6: CN1.13 (BUS6), U4.12 (B6)
/BUS7: CN1.14 (BUS7), U4.11 (B7)
/CBL_A0: J1.2, RN1.16 (R1.2)
/CBL_A1: J1.4, RN1.15 (R2.2)
/CBL_A2: J1.6, RN1.14 (R3.2)
/CBL_A3: J1.8, RN1.13 (R4.2)
/CBL_BUS0: J1.20, RN2.16 (R1.2)
/CBL_BUS1: J1.22, RN2.15 (R2.2)
/CBL_BUS2: J1.24, RN2.14 (R3.2)
/CBL_BUS3: J1.26, RN2.13 (R4.2)
/CBL_BUS4: J1.28, RN2.12 (R5.2)
/CBL_BUS5: J1.30, RN2.11 (R6.2)
/CBL_BUS6: J1.32, RN2.10 (R7.2)
/CBL_BUS7: J1.34, RN2.9 (R8.2)
/CBL_CLK: J1.16, RN1.9 (R8.2)
/CBL_INH_REQ: J1.18, R2.1, U5.2 (I1)
/CBL_~MATCH: J1.10, RN1.12 (R5.2)
/CBL_~RI: J1.14, RN1.10 (R7.2)
/CBL_~RO: J1.12, RN1.11 (R6.2)
/CLK: CN1.6 (CLK), J3.4, U3.9 (A7), U5.1 (I0/CLK)
/DIR: U4.1 (A->B), U5.18 (I/O)
/INH: CN1.3 (INH), J3.1, U5.15 (I/O)
/USER: CN1.4 (USER), J1.38
/XBUS0: RN2.1 (R1.1), U4.2 (A0)
/XBUS1: RN2.2 (R2.1), U4.3 (A1)
/XBUS2: RN2.3 (R3.1), U4.4 (A2)
/XBUS3: RN2.4 (R4.1), U4.5 (A3)
/XBUS4: RN2.5 (R5.1), U4.6 (A4)
/XBUS5: RN2.6 (R6.1), U4.7 (A5)
/XBUS6: RN2.7 (R7.1), U4.8 (A6)
/XBUS7: RN2.8 (R8.1), U4.9 (A7)
/~EN: R1.2, SW2.2 (B), U5.6 (I5)
/~MATCH: U3.6 (A4), U5.16 (I/O)
/~NIB: U2.19 (P=R), U5.8 (I7)
/~OE_245: U4.19 (CE), U5.17 (I/O)
/~PAGE: U1.19 (P=R), U5.7 (I6)
/~RESET: CN1.5 (~RESET), J1.36
/~RI: CN1.32 (~RI), J3.3, U3.8 (A6), U5.5 (I4)
/~RO: CN1.31 (~RO), J3.2, U3.7 (A5), U5.3 (I2)
GND: C1.2, C2.2, C3.2, C4.2, C5.2, C6.2, CN1.1 (GND), J1.1, J1.3, J1.5, J1.7, J1.9, J1.11, J1.13, J1.15, J1.17, J1.19, J1.21, J1.23, J1.25, J1.27, J1.29, J1.31, J1.33, J1.35, J1.37, J1.39, J1.40, J2.2, J3.6, R2.2, RN3.1 (common), SW2.1 (A), U1.1 (G), U1.3 (R0), U1.10 (GND), U2.1 (G), U2.10 (GND), U2.11 (P4), U2.12 (R4), U2.13 (P5), U2.14 (R5), U2.15 (P6), U2.16 (R6), U2.17 (P7), U2.18 (R7), U3.10 (GND), U3.19 (CE), U4.10 (GND), U5.4 (I3/PD), U5.9 (I8), U5.10 (GND), U5.11 (I9/~OE)
unnamed: F1.1, JP1.1 (A)

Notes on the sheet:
Spare 68 Ω packs for RN1/RN2, BOM only (not on the board). Swap one into the RN1 or RN2 socket if 33 Ω shows ringing on the scope.
Power connector to breadboard

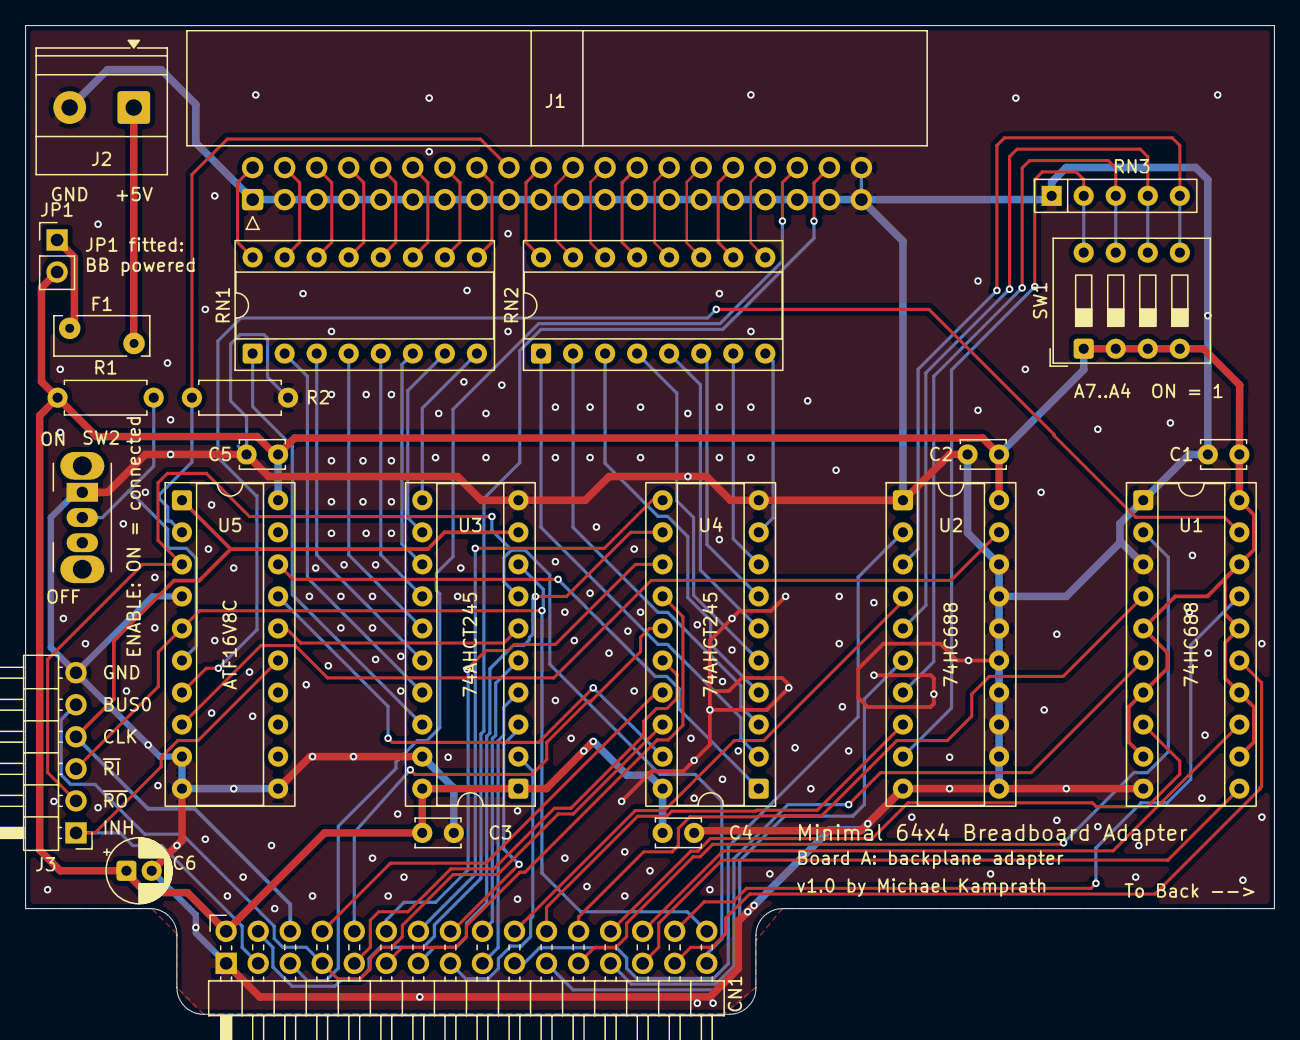
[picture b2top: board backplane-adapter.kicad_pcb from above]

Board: 2 copper layers, 99.0 x 78.4 mm, 24 parts (0 on the bottom side), 77 nets.
